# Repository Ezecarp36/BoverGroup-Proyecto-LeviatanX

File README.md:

# BoverGroup-Proyecto-LeviatanX
El Bover Group, compuesto por tres estudiantes de Septimo año de la E.E.S.T.Nº5 "2 DE ABRIL", se encuentra desarrollando un emocionante proyecto "LeviatanX" se trata en principio de un proyecto de varias etapas la primera es la realizacion de un drone controlado por radiocontrol para su uso en monitoreo y vigilancia. El proyecto será presentado en la materia Proyectos Electrónicos, dirigida por el Ing. Martin Leguizamón. Los integrantes del grupo son Leandro Benitez, Ezequiel Sierra y Gabriel Romero, quienes trabajan juntos para en un futuro automatizar el drone, permitiéndole volar de manera autónoma y a esto agregar la utilizacion de una cámara para reconocimiento con machine learning en tareas de monitoreo y vigilancia. Este proyecto tiene como objetivo ser un gran avance en la tecnología de drones, demostrando su creatividad y trabajo en equipo.
Tenemos un drive el cual plasmamos la informacion de los componentes usados y la documentacion necesaria para llevar a cabo el proyecto:
Drive: https://drive.google.com/drive/folders/1-x7SCu_ywuLYVk6GRU4Gz9AUGYImAjfw?usp=drive_link

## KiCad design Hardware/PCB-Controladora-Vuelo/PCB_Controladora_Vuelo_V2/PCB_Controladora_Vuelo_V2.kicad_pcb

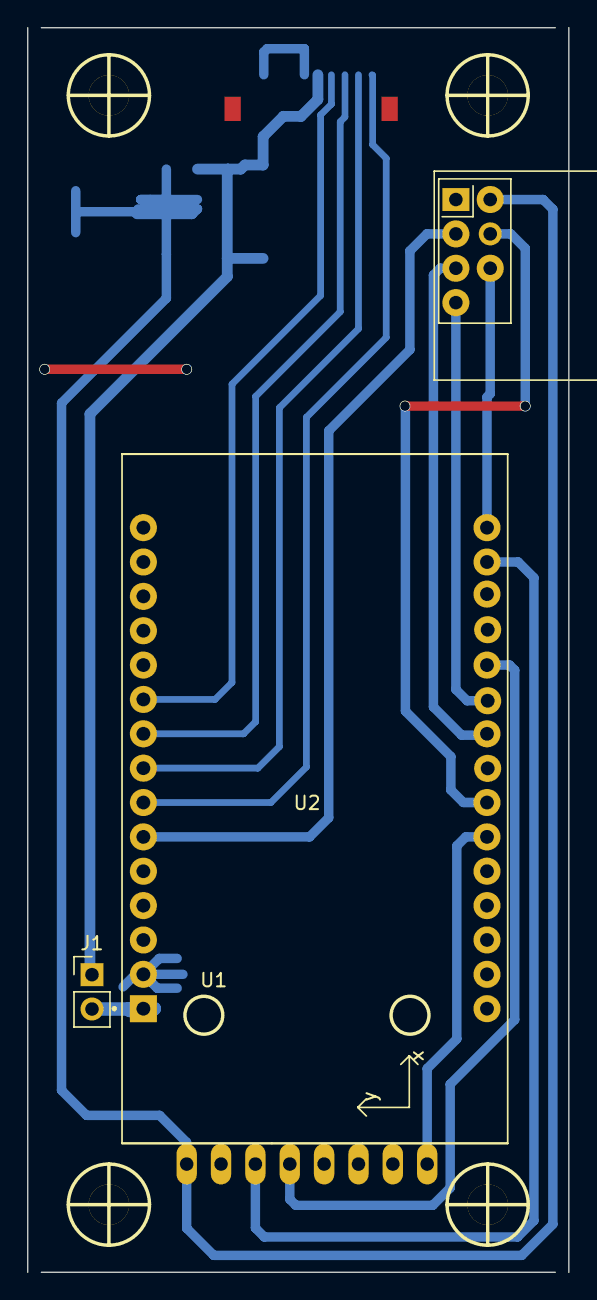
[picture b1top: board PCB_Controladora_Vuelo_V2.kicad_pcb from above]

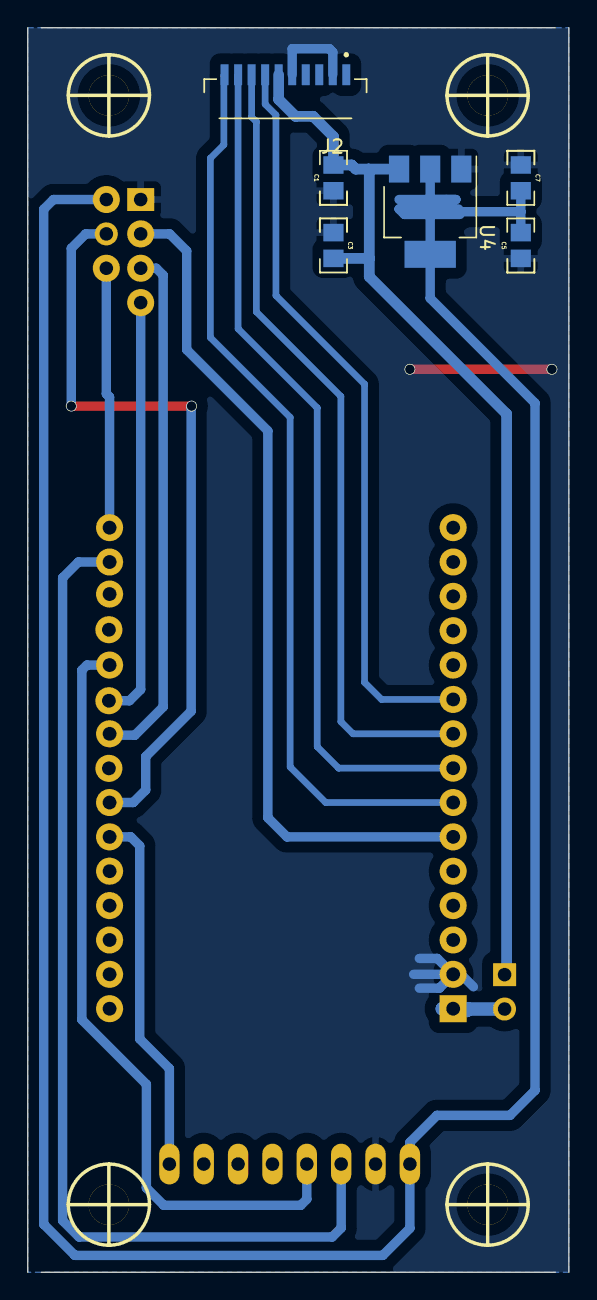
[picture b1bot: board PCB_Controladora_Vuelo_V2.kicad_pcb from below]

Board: 2 copper layers, 40.0 x 92.0 mm, 14 parts (6 on the bottom side), 16 nets.

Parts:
C1, C5: 10uF; C_0805
C3, C7: 100nF; C_0805
H1, H2, H3, H4: Mounting_Hole; hole_3mm
J1: Jumper Serial; PinHeader_1x02_P2.54mm_Vertical
J2: ESC; JST10mm
U1: MPU-5060; MPU-6050
U2: ESP32-DEVKIT-V1; ESP32-DEVKIT-V1-30Pines
U3: Nrf24l01; nRF24L01_Breakout
U4: AMS1117-3.3; SOT-223-3_TabPin2

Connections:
+3V3: C5.1, C7.1, U1.1 (VCC), U3.2 (VCC), U4.2 (VO)
+5V: C1.1, C3.1, J1.1, J2.6, U4.3 (VI)
/CE_NRF24L01: U2.6 (D27), U3.3 (CE)
/CSN_NRF24L01: U2.24 (TX2), U3.4 (CSK)
/INT_MPU6050: U1.8 (INT), U2.25 (RX2)
/Jumper_Serial: J1.2, U2.1 (VIN)
/MISO_NRF24L01: U2.21 (D19), U3.7 (MISO)
/MOSI_NRF24L01: U2.16 (D23), U3.6 (MOSI)
/S1_MOTOR: J2.7, U2.10 (D32)
/S2_MOTOR: J2.8, U2.9 (D33)
/S3_MOTOR: J2.9, U2.8 (D25)
/S4_MOTOR: J2.10, U2.7 (D26)
/SCK_NRF24L01: U2.22 (D18), U3.5 (SCK)
/SCL_MPU6050: U1.3 (SCL), U2.17 (D22)
/SDA_MPU6050: U1.4 (SDA), U2.20 (D21)
GND: C1.2, C3.2, C5.2, C7.2, J2.2, J2.5, U1.2 (GND), U2.2 (GND), U2.29 (GND), U3.1 (GND), U4.1 (GND)

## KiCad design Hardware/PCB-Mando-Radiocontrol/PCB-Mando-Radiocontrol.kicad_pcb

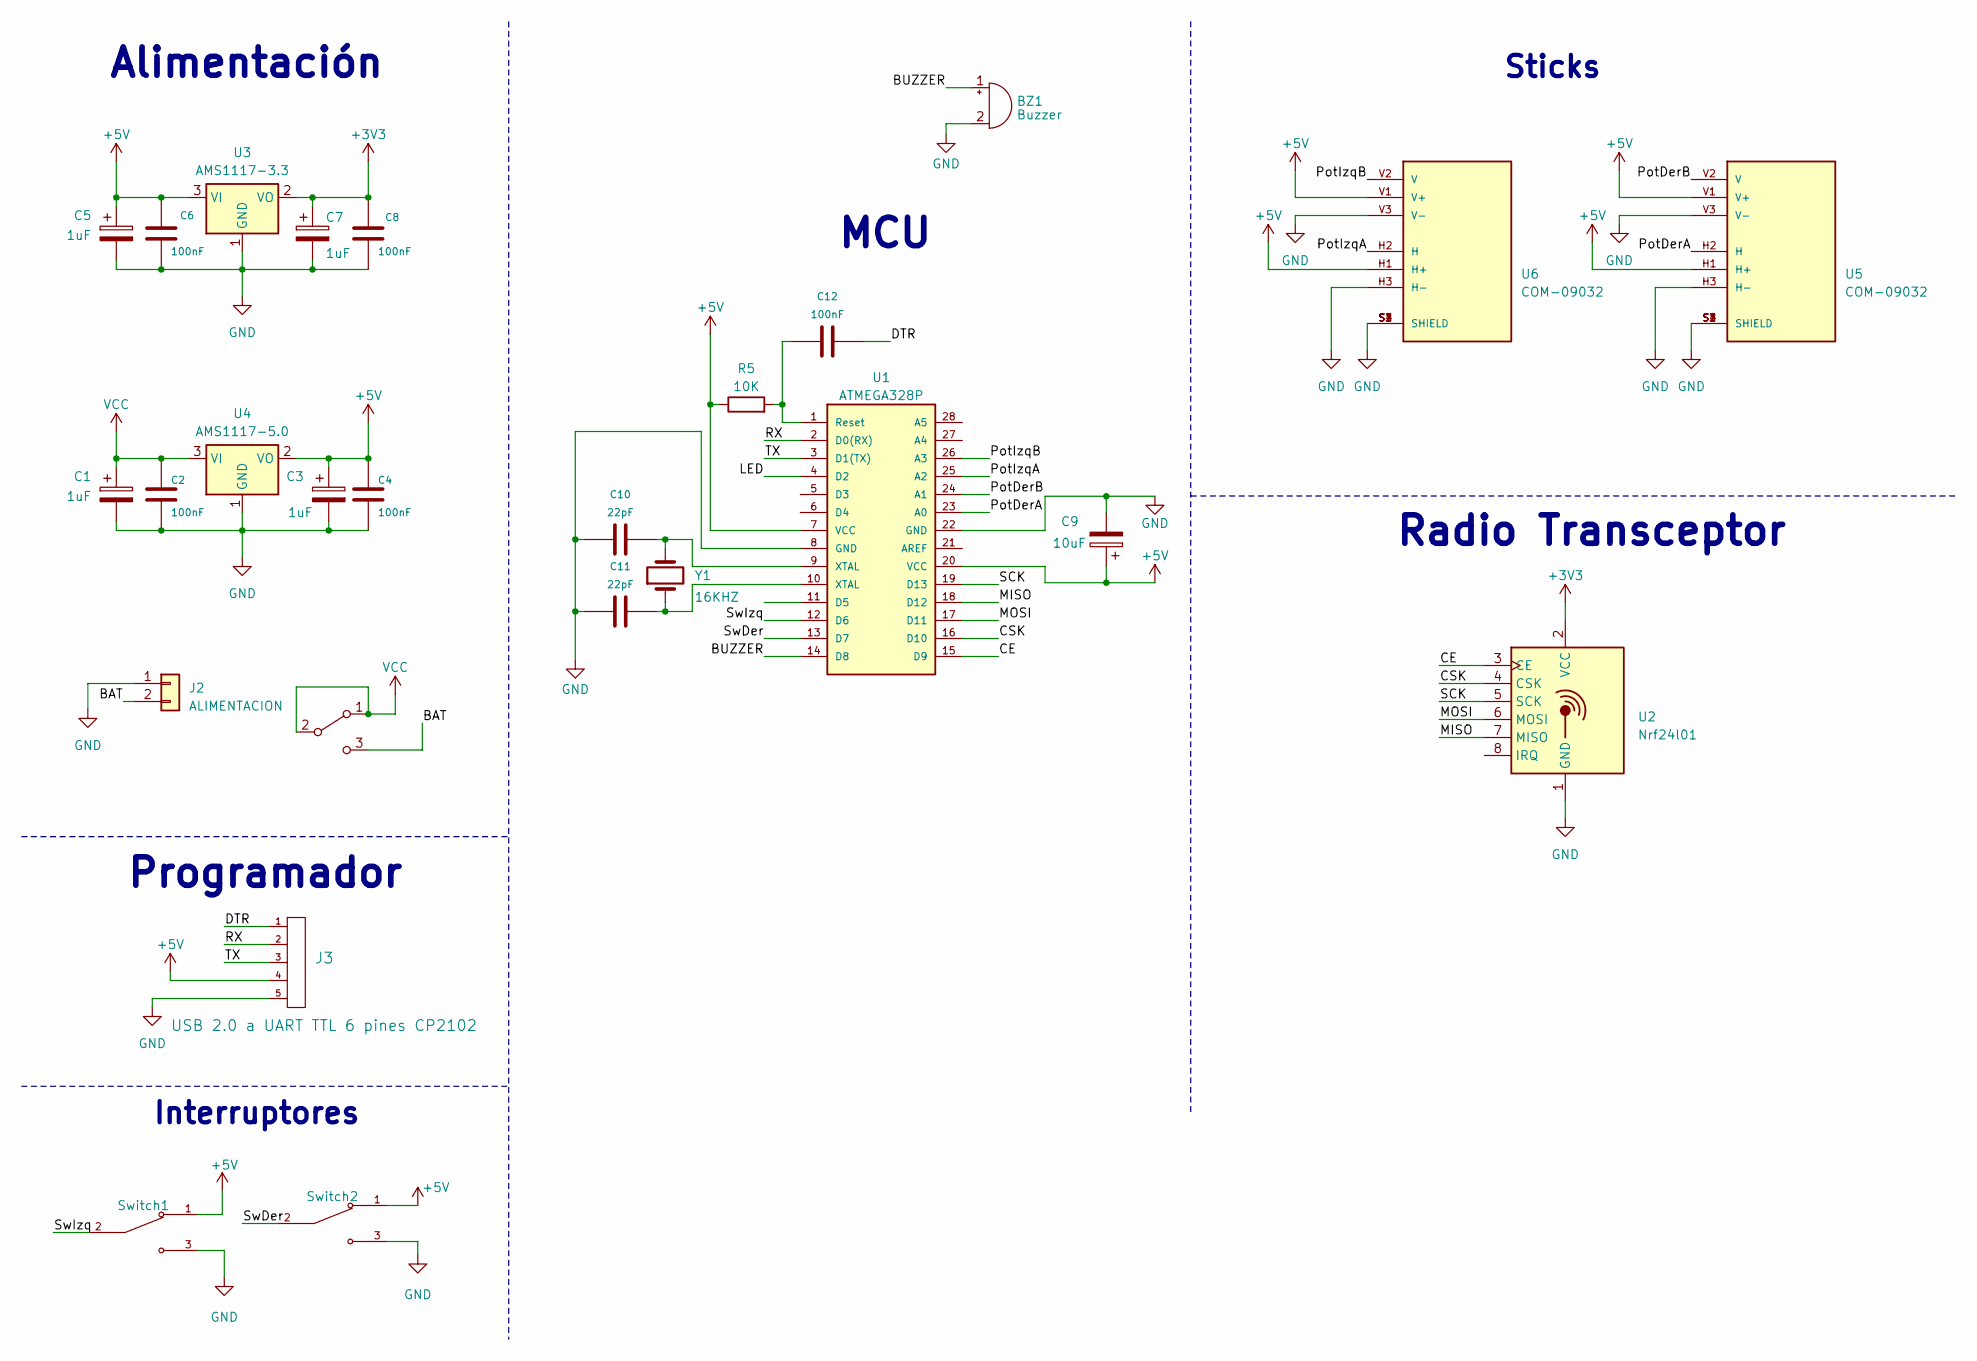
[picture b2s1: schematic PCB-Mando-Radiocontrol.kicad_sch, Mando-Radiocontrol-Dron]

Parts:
BZ1: Buzzer; Buzzer_12mm
C1, C3, C5, C7: 1uF; CAP_ELEC_5x11mm
C2, C4, C6, C8, C12: 100nF; C_1206_3216Metric
C9: 10uF; CAP_ELEC_5x11mm
C10, C11: 22pF; C_1206_3216Metric
J2: ALIMENTACION; JST_PH_B2B-PH-K_1x02_P2.00mm_Vertical
J3: USB 2.0 a UART TTL 6 pines CP2102; Pin_Header_5
R5: 10K; R_1206_3216Metric
SW1: SW_100SP3T1B1M2QE
Switch1, Switch2: SW_100SP3T1B1M2QE; PARTREV B
U1: ATMEGA328P; DIP_28-300_socket
U2: Nrf24l01; nRF24L01_Breakout
U3: AMS1117-3.3; SOT-223-3_TabPin2
U4: AMS1117-5.0; SOT-223-3_TabPin2
U5, U6: COM-09032; XDCR_COM-09032; PARTREV N/A
Y1: 16KHZ; XTAL_XT9S20ANA16M

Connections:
+3V3: C7.1, C8.1, U2.2 (VCC), U3.2 (VO)
+5V: C3.1, C4.1, C5.1, C6.1, C9.1, J3.4, R5.1, Switch1.1, Switch2.1, U1.7 (VCC), U1.20 (VCC), U3.3 (VI), U4.2 (VO), U5.H1 (H+), U5.V1 (V+), U6.H1 (H+), U6.V1 (V+)
/BAT: J2.2, SW1.3 (C)
/BUZZER: BZ1.1 (-), U1.14 (D8)
/CE: U1.15 (D9), U2.3 (CE)
/CSK: U1.16 (D10), U2.4 (CSK)
/DTR: C12.2, J3.1
/LED: U1.4 (D2)
/MISO: U1.18 (D12), U2.7 (MISO)
/MOSI: U1.17 (D11), U2.6 (MOSI)
/PotDerA: U1.23 (A0), U5.H2 (H)
/PotDerB: U1.24 (A1), U5.V2 (V)
/PotIzqA: U1.25 (A2), U6.H2 (H)
/PotIzqB: U1.26 (A3), U6.V2 (V)
/RX: J3.2, U1.2 (D0(RX))
/SCK: U1.19 (D13), U2.5 (SCK)
/SwDer: Switch2.2, U1.13 (D7)
/SwIzq: Switch1.2, U1.12 (D6)
/TX: J3.3, U1.3 (D1(TX))
GND: BZ1.2 (+), C1.2, C2.2, C3.2, C4.2, C5.2, C6.2, C7.2, C8.2, C9.2, C10.1, C11.1, J2.1, J3.5, Switch1.3, Switch2.3, U1.8 (GND), U1.22 (GND), U2.1 (GND), U3.1 (GND), U4.1 (GND), U5.H3 (H-), U5.S1 (SHIELD), U5.S2 (SHIELD), U5.S3 (SHIELD), U5.S4 (SHIELD), U5.V3 (V-), U6.H3 (H-), U6.S1 (SHIELD), U6.S2 (SHIELD), U6.S3 (SHIELD), U6.S4 (SHIELD), U6.V3 (V-)
unnamed: C10.2, U1.9 (XTAL), Y1.2
unnamed: C11.2, U1.10 (XTAL), Y1.1
unnamed: C12.1, R5.2, U1.1 (Reset)
VCC: C1.1, C2.1, SW1.1 (A), SW1.2 (B), U4.3 (VI)

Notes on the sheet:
Radio Transceptor
Alimentación
MCU
Programador
Interruptores
Sticks

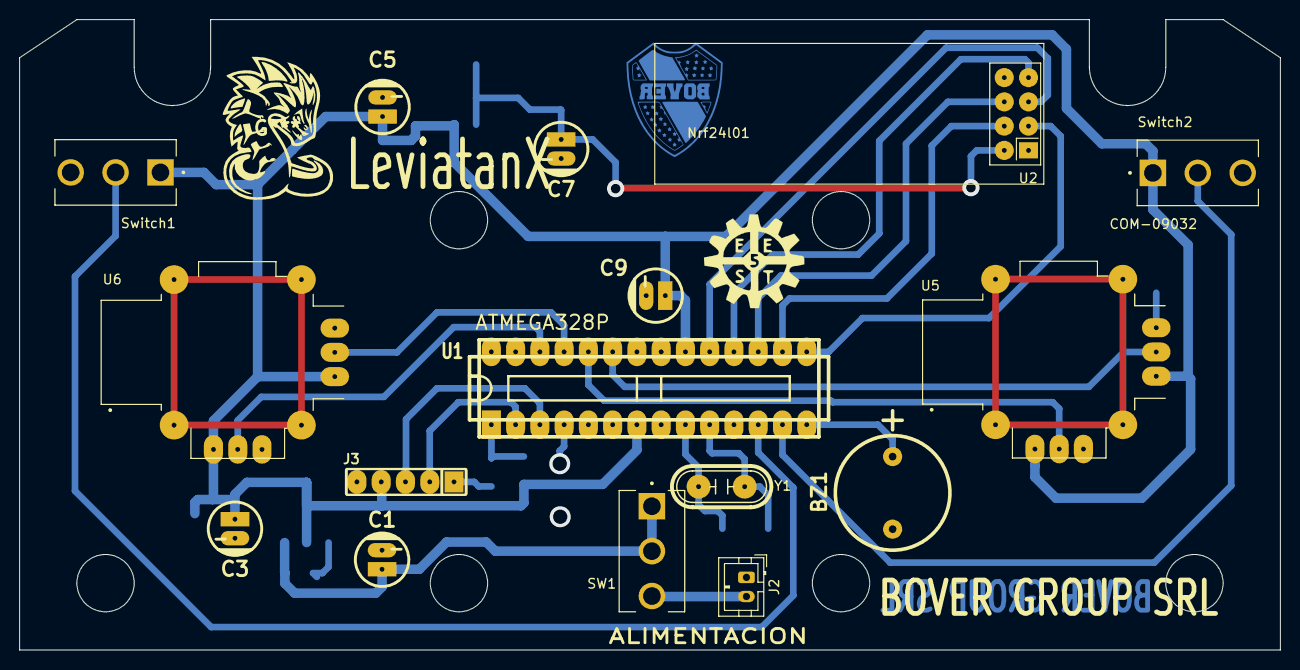
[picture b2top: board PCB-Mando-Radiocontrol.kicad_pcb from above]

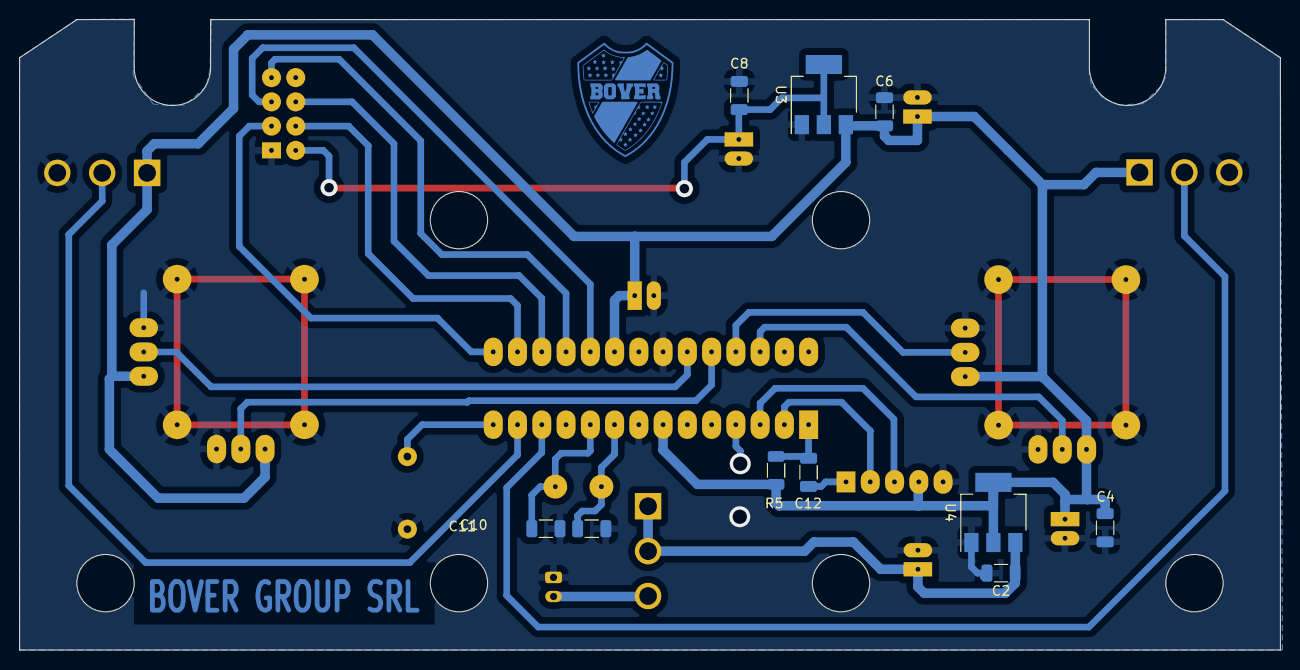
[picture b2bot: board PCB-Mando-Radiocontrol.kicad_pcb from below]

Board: 2 copper layers, 132.0 x 66.0 mm, 26 parts (10 on the bottom side), 23 nets.

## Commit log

2023-04-12 Comenzamos con el PCB del mando Radiocontrol
2023-04-12 empiezo con el sch de la controladora de vuelo
2023-04-12 sin cambios
2023-04-13 esquematico del pcb del radiocontrol terminado, falta acomoda los componentes y empezar el pcb
2023-04-13 esquematico terminado y ordenado
2023-04-14 arregle errores de orden y los capacitores queda resolver conexiones si son las correctas , en programador y mcu
2023-04-14 huellas asignadas correctamente
2023-04-14 SCH terminado y PCB a continuar
2023-04-14 Ordene un poco y agregue las librerias de los simbolos y footprints que faltaban
2023-04-14 Inicio del PCB del radiocontrol
2023-04-14 Corregi unos errores
2023-04-14 agregue unas imagenes a la carpeta del pcb del radiocontrol
2023-04-14 Ordene mejor las carpetas
2023-04-15 Cambios en el kicad_sch realice cambios del programador y del capacitor de filtro para el uC ademas rellene el rotulo
2023-04-15 cambios en el sch de la Controladora de Vuelo se agrega a la rama los cambios hechos por eze y ademas agregue la alimentacion y ordene, me quedan las conexiones y hacer el symbolo de la controladora 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
2023-04-17 Agregue conexiones i2c imu y spi transceptor tambien modifique la alimentacion por vin para el uC
2023-04-17 Avances en el PCB de la controladora de vuelo
2023-04-18 Reordenamiento de componentes
2023-04-18 En proceso de ordenamiento de componentes
2023-04-18 subo cambios hechos en legui solucione mpu y lugar esp32 mal Footprints
2023-04-19 Realice cambios de huella ESP32 y Symbol
2023-04-19 muchos cambios leer saque todos los NC y coloque X ya que al poner etiquetas nc reconoce como que debe haber una conexion entre ellos y nqv tambien digamos que hice una buena 1ra parte de pcb, que se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
2023-04-19 Trabaje en el PCB corriegindo ordenes faltaria ver si se pueden agregar pines y corregir que no existan riesgo al momento de planchar o por un corto o abrirse el circuito
2023-04-19 PCB a medida con componentes a ordenar
2023-04-21 Errores en el esquematico corregidos
2023-04-21 SCH corregido, PCB en proceso a falta de NRF
2023-04-22 Hice una mejora con un solo puente de pista 3,3v para transeptor en donde existen riesgos pero mañana trato d mejorar y chequear pines asi se mergea
2023-04-24 MODIFIQUE ESQUEMATICO Y PCB FINALIZADO DIRIA yo falta aprobacion de legui lo deje con 2 puentes para mas seguridad , nuevo puente pin MOSI NRF24L01 Y PLACA LISTA CHEQUEO EL 3D Y VAVVAVVAVA
2023-04-24 SCH Completo, PCB en proceso en un ~80%
2023-04-24 SCH completo, PCB en proceso ~80% completado
2023-04-24 Cambie capacitores y agregue componentes smd , quedo bien cambie los capacitores electroliticos , queda duda de la huella jst y el posicionamiento de los agujeros de sujecion y ajustar la placa a un 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
2023-04-24 borre librerias 3d innecesarias
2023-04-24 comitear cambios
2023-04-24 SCH completo, PCB en proceso ~90% completado
2023-04-24 realice modificaciones desde 0 en el PCB a continuar por leandro, es una placa en paralelo a la de gabi
2023-04-25 realice la base final de la placa , ordene cosas y cambie pines me falta agregar dos switches y ordenar y corroborar todo
2023-04-25 empece a realizar pruebas con la MPU y agregue varios codigos de ejemplo
2023-04-26 limpie nombres y subcarpetas
2023-04-26 aplique sugerencias de markow y mias, agregue botones modifique esquematico y pcb
2023-04-26 Todos los ejemplos de la IMU probados, solo falta corregir la lectura del eje Z, la cual no logro obtener de forma correcta
2023-04-26 resolviendo problemas de merge
2023-04-26 hubo un problema en el repositorio, subo la carpeta de la controladora de vuelo terminada nuevamente
2023-04-27 solucionando problemas
2023-04-27 agregue el readme nuevamente
2023-04-27 Ordene serigrafia y cambie los capacitores c11 y c12 tht por cmd
2023-04-28 Agregue LED y BUZZER , pcb listo para montar
2023-04-28 aGREGUE LOGO DE bover group srl en B.CU
2023-04-28 Agregue serigrafia y ordene
2023-04-28 Agregue el svg de la placa del radiocontrol
2023-04-28 Subo archivo svg de SERIGRAFIA
2023-04-28 corregi svg de serigragia de radiocontrol
2023-04-30 elimine la carpeta de librerias para ordenar todo mejor
2023-05-01 Create README.md
    Se habia borrado accidentalmente, hay que pasarlo a Ingles
2023-05-01 Realice correciones para las impresiones en el puerto serial, llegue a calibrar por medio de CalibrarOffSets pero no entendi
2023-05-01 probe el filtro complementario responde bien, podria mejorar
2023-05-01 modifique rango de mediciones
2023-05-01 agrego calibracion DPM
2023-05-02 agregue ejemplos del modulo nrf24l01
2023-05-06 agrego pruebas lean, donde realizare nuevos avances con la mpu para lograr entender conceptos por mi cuenta
2023-05-07 aplique filtro complementario en pruebas lean, voy cazando el tema
2023-05-07 el yaw no me gusta como lee, los demas safan con un filtro complementario
2023-05-07 empiezo a ordenar la carpeta y creo archivo calibracion simple
2023-05-07 intentando calibrar mpu, por ahora nada
2023-05-07 ROBEEE RIBER ROBEEEE, HERRERA LA CONCHA DE TU MADRE
2023-05-08 Codigo a probar para Nrfl2401 ESP32
2023-05-13 ordene, corregi y subi codigo de transmicion a atmega328p
2023-05-13 DECLARE BIEN LOS PINES DEL ATMEGA
2023-05-13 prueba de transmisor y receptor one
2023-05-13 prueba 2
2023-05-13 eerror
2023-05-14 Update PruebaRadioTransmisor.ino
    Comentarios explicativos del código
2023-05-14 Update PruebaRadioReceptor.ino
    Comentarios descriptivos del código
2023-05-15 test 3 , no funciona la conexion por ahora
2023-05-15 test gabi
2023-05-27 Funciono correctamente la conexion entre el radiocontrol y el receptor, y agregue un codigo para controlar el motor con el acelerador del control
2023-05-28 Agrego cambios en el esquematico de la nueva version de la controaldora de vuelo 2.0
2023-05-28 Cambie pines i2c mpu6050 , hay que probarlos y cambie conexiones de nrf que funcionan, mejore las medidas para el frame
2023-05-28 cambie pines sda y scl para evitar conflictos wifi
2023-05-28 configuracion mpu6050 a testear con nuevos pines i2c y INT
2023-05-29 ultimo codigo probado , comunicacion bien habia rudio en los grados de la imu
2023-05-30 placa realizada en taller , prueba de pines
2023-05-30 codigo de comunicacion spi entre nrf joya, pines joya
2023-05-30 comunicaciion i2c del modulo mpu6050 bien. tiene un toque de ruido en milesima de grado pero se mejora
2023-05-30 CAMBIOS DE NOMBRES
2023-05-30 CAMBIOS
2023-05-31 prueba a motor 2 , antes probe y no andaba la velocidad baja, pitaba el motor
2023-05-31 anda, pero la vel de 1000 no
2023-05-31 prueba exitosa velocidad de trabajo 1100 a 1800 por ahora no probe mas de 1800
2023-06-01 testeando comunicacion rf y motores
2023-06-01 ordeno carpetas
2023-06-02 hice un filtro de promedios para la lectura del acelerador
2023-06-02 Modificaciones finales en la V2 del PCB de la FC
2023-06-02 agregue el trazado de la placa SVG
2023-06-02 test escalado de velocidad
2023-06-02 revisar
2023-06-02 no anda el escalado todavia , pero no se si es necesario
2023-06-02 Corrección en un codigo de prueba
2023-06-03 AGREGO LIBRERIAS ARDUINO
2023-06-03 salida esc anda bien
2023-06-03 comento codigo de receptor
2023-06-03 comento codigo del transmisor
2023-06-03 transmisor
2023-06-04 mañana sigo con agregar ti a la libreria y empezar a ordenar codigo y entender el codigo de la mpu
2023-06-04 arregle libreria pid y realice cambios en pruebaspid
2023-06-05 comento libreria
2023-06-05 AVANZANDO
2023-06-05 avanzando con logica de pid pitch
2023-06-05 compilo, nose si funciona je, cambios en libreria y codigo de prueba PID a full
2023-06-05 comentando codigo pruebas pid
2023-06-05 identando codigo
2023-06-05 mañana paso parte de codigo a funciones y trato de armar una libreria para la mpu
2023-06-05 AGREGO BOTON START
2023-06-05 CAMBIOS PARA APAGAR PRUEBA
2023-07-03 agrego 3d base mando
